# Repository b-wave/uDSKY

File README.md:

# uDSKY PROJECT
## A Physical implementaion of an Apollo AGC DSKY. 
*...with USB 2.0 Connectivity for PC simulators*

This assembly and firmware has sucessfully been used to control both
John Pultorak's Block1 Simulator vers 1.16 in C++ and Ronald Burkey's
Block 2 AGC simulators on <http://www.ibiblio.org/apollo/> 
Further, the Simulation runs great on Raspberry Pi.  I forked the 
files needed for both simulators. <https://github.com/b-wave/virtualagc> 

I mainly run it on a Rapsberry PI with the intention of embedding the Pi in this chassis. I started a 
python script that will run the software so I don't have to start the virtual AGC program.... 
now that is a *work in progress...stay tuned* 

The Teensy 3.2 used in this has a plug in board that contains a Real time clock and navigation sensors.
<https://www.pjrc.com/store/prop_shield.html>  Which will mount to the board nicely.  I also included a couple of Apollo-themed Processing PDEs in <https://github.com/b-wave/uDSKY/tree/master/uDSKY%20IMU>
that work with this board and it can mount to the uDSKY using stacking header pins. 

Why on earth did I do this project?  Ultimately, it is a clock. I intend to have a standalone
version to do navigation demonstation experiments and become a "moon clock" to track
the current position, phase, and distance to the moon - *...in real time!*

### What it is not... 
Its not to scale or even a 1:1 scale model of a DSKY.  How I arrived at the scaling was 
I took the best head-on photo of a DSKY I could find and scaled it to match the 
smallest descrete LED 7-segment *green-ish* displays I could find.
It turned out that at that scale, the Keys were  ~.75" on center, which was nice
eand almost exactly 0.75" Square. Also by happy accident the Teensey fits between the top LED
Displays. The front panel measurments was about 7.0" x 6.5" so about, but
not exactly, half the size of a real DSKY. You will see some early refernces to **mini-DSKY** 
Which is the same thing as **uDSKY**.  The whole thing sandwiches nicely together
using plexiglas plates - which I will provide laser cut patterns for - and #4 AWG hardware spacers.

The **uDSKY** assembly is remarkably sturdy and even kind of hefty too.  The keys and circuit 
boards were attached by small torx head "thread rolling" screws for plastic.  
The Torx heads allow for close proximity to components and I think a little easier to install straight.
The hardware I used were surplus and about 2 AWG, ( for a 1/16" pilot hole) and 1/8" long.  
I got them on e-bay and i don't have the link, there were 100's of them in a box for a few dollars. 
They should be easy to find. I'll update a link if I find a good supplier again. 

There are two other circuit boards I am developing.  The INDICATOR boards for the LEDs
since I used perf boards for this prototype.  The POWER REGULATOR board for stand alone
operation on 12V dc, and illuminating and controlling the VERB, NOUN, and PROG LEDs
and the keyboard backlighting. Since these are a lot of LEDs involved 12V is used for them. 
These will be controlled the same as the other LEDs using two of the non used DP signals
but thru an isolator to control 12V to theses diodes. I also have an idea to use LEDs
and some clear plexiglas to simulate the long EL strips between the three registers - 
 but this is still in the *idea phase*...but the testing is showing promise. 

uDSKY in action 9/20/19 on the 50th moonlanding, running on rPI and ran the *actual* Apollo 11 software (C055), mostly P00 for the entire duration of the flight.   This .gif was when they would have been in lunar orbit at 100hrs 38mins or so MET. 

Running Apollo 11 CMD Module Software. 

The circuit boards are mostly attached to a 1/8" plexiglas rear plate.  The Teensey is
mounted on female pin headers on the main display board.  The Teensy actully slips thru
a recetangular hole in the rear mounting plate. 

## Displays
The displays are multiplexed with the DP segments from the first two controlling the LED INDICATORS.  Each lamp is controlled by the decimal point signals, which were not used in the original Apollo DSKY display.  This turned out to be a good parts reduction
as all the segments and Indicators can be controlle by only 3 LED controller chips.

All Displays are ON!

Only the SEGMENT G and DP are used in the first display for each of the three registors
to provide the segments for the SIGN digit.  Since there is no known compatable SIGN LED Display - i put an array of SMT LEDs on the circuit board to represent this digit.

Every Other INDIC Lamp is On.

As you can see there is still some leakage between wells of the Indicator lamps but 
this is quite usable. 

The lamps are separated with a matrix of opaque lattius.  I made the prototype with popcicle
sticks, which turned out to be a litle short.  I made a 3D printed chassis wich is way better! 

Indicator Display Mask

In all the dispalys work fine, but later I realized that if the displays were behind a card stock printout, behind some smoked grey plexiglas they look a lot like the original Apollo DSKY EL displays.  But the LEDs were too far from the card stock to be seen.  I then developed a pair of circuit boards, one to hold the LEDs and the other provides a light mask. This brings the sign digit near to the display. 67lb. White Cover Card stock (Staples **Item 679482** to be exact).  I 

As you can see with the card stock the uDSKY is very simular to the DSKY as you cant really see the digits until they are
illuminated.  The only issue is the LED must be against the card stock for the effect to work.  I did not have the sign LED digit boards working, and the prototype had the LEDs soldered to the main board, which is too far away to be seen thru the card stock.  

*No digits seen With power off*

The 3D printed chasis is now on version 2.  Here are a couple of shots of the first parts.  It really started looking real, and as you can see from the .gif it is a lot better now than the original hand cut plexiglas. 

3D Parts

Keys and displays added

# Apollo uDSKY's  Keys 
The Keys are Cherry MX series. These have a real nice clicky feel and best of allthey can support custom keycaps and can be illuminated! 

#The key caps are from:  <http://xkeys.com/accessories/Keycaps.php> 
They are not .75" x .75 which would be ideal but they have a little curve on the bottom
which makes the laser printed labels a little tricky to line up. But it works fairly well.
You will need 19 caps (4 orders will get you 20). I got both the clear and green. I thnk the black ones
owill be opaque so they can't be illuminated. 

<Keys with relegendable keycaps for cherry mx switches

The Keys are simply mounted on an *OSH Park Version*  of the SF MX breakout board. You can order them 
#or (BOB-13773) they are identical: https://www.sparkfun.com/products/13773 The next version I make may contain all 19 keys in one board.  The 1 pins are all connected for ROWS and the 2 pins are for columns.
Check out the Teensey code for the pattern and hookup. 
<https://github.com/b-wave/uDSKY/tree/master/DSKY%20Arduino%20Files>

Breakout Column connections - using the 2 Pads.

The X/Y row - column pattern is fairly self-explanitory.  The final assembly feels like holding some chain-mail armor. 
The only difficulties were to use small wire "U" shapes instead of straight from pin to pin. This makes the 
spacing of the keys line up to the holes on the base plate a little eaiser.  The second is the two columns 
on the ends don't line up anyway on one side, it helps to flip those two end keys, the pads match and the keycap will
still go on correctly. *NOTE: see the flip keys on on the right hand side of bottom view:*

Matrix of Keys

# Apollo uDSKY's  Registers Sign Digits
I developed a little circuit board *set* that will give a sign digit for each register.  There are actully two other ways to 
get the sign digits. First, simply put in another 7-segment display. The G segment will be (-) and the DP will represent (+) 
...*blank is octal as usual*  Second, the board has pad for SMT LEDs that form the signs.  G and DP illumiate the pairs of
LEDs but this arrangement has the distance problem, but you can still use the mask board to make the displays look better.

This board will allow a pretty good substitute for the non-existent compatible LED sign digits for an **Apollo DSKY** display.  You will also need the   **DS_MASK.brd** <https://oshpark.com/shared_projects/6qTKqnak> for each display if you want the displays to be more *segment-ty?*   There are also some additional masking and diffusing techniques  that can be done to make these look really good.

##
This board set are intended to be used with a 0.39" 10-pin LED displays such as **LTS-4301G** that were used on the **uDSKY** display. 

The minus **(-)** are controlled by the standard *G - Segment* Pin **1** with 2 LEDs in series.  The **(+)** is a combination of the **"g1"**  and **"g2"** Segs *and* the vertical segments *(some times referred to as **"h"** and **"J"**)* which are connected to the **"DP"** pin **6**.  The **Common** pins are **8** and **3**.  Because both displays are *two* LEDs in series this should simplify non-MUX displays as well.

<https://www.jameco.com/z/LTS-4301G-Lite-On-Electronics-Green-7-Segment-LED-Display_2227911.html>

When selecting the SMT LEDs make sure you get them close to the brightness and color wavelength.  For example , these LED displays have: **569 nm**  (green) with an avg. intensity = **2200 µCD** @ If =10mA.

I can post some details on how to put these together.  But basically, you need to diffuse the light or the viewing angle gets critical.  A simple piece of scotch tape but hot melt glue may also work.  

The parts placement is pretty simple, The anode of the first LED connects to the respective pin.  The two LED's cathodes and anodes for each segment are connected together. The cathodes of the 2nd LEDs connect to the common pins.  If you forget one LED or get one in backwards it's like Christmas tree light strings... *no light for you!*  

Plus Display

A couple of baffles between the G and the vertical segments are also needed or when only (-) is displayed the other segments are still slightly visible.  I used a couple scrap pieces of black wire insulation wedged between the segments to block this.  The messy dabs of hot melt glue used to hold these in place are also visible.

Light Baffels 

Minus Display

Two 0.1" 5-pin headers to hold the two boards together.  Mount the header on *top* of this board (long pins go thru the board)   Then put the mask board on top of the header. The boards are separated by the plastic header. Push the pins flush to the  top **MSK_Brd** *Pins 1, 6, 8, and 3* now have to be soldered on the bottom of this board.  You can solder the mask board's pins all in place if you want to - after you verify everything is working OK of course, there are no electrical connections to any other pads.

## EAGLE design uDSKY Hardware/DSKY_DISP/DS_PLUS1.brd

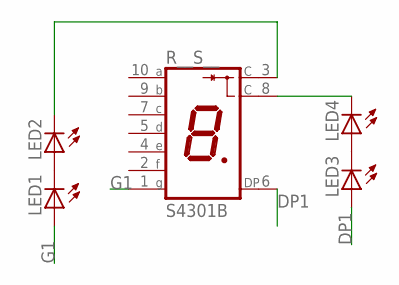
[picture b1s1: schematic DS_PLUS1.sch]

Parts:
LED1, LED2, LED3, LED4: LEDCHIP-LED0603; CHIP-LED0603
R__S__: S4301B

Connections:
DP1: LED3.A, R__S__.6 (DP)
G1: LED1.A, R__S__.1 (G)
unnamed: LED1.C, LED2.A
unnamed: LED3.C, LED4.A
unnamed: LED4.C, R__S__.8 (C)
unnamed: LED2.C, R__S__.3 (C)

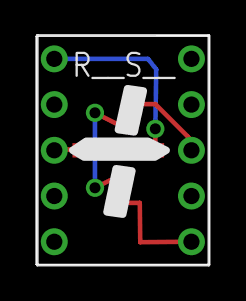
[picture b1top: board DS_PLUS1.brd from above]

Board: 2 copper layers, 9.7 x 12.7 mm, 5 parts (0 on the bottom side), 6 nets.

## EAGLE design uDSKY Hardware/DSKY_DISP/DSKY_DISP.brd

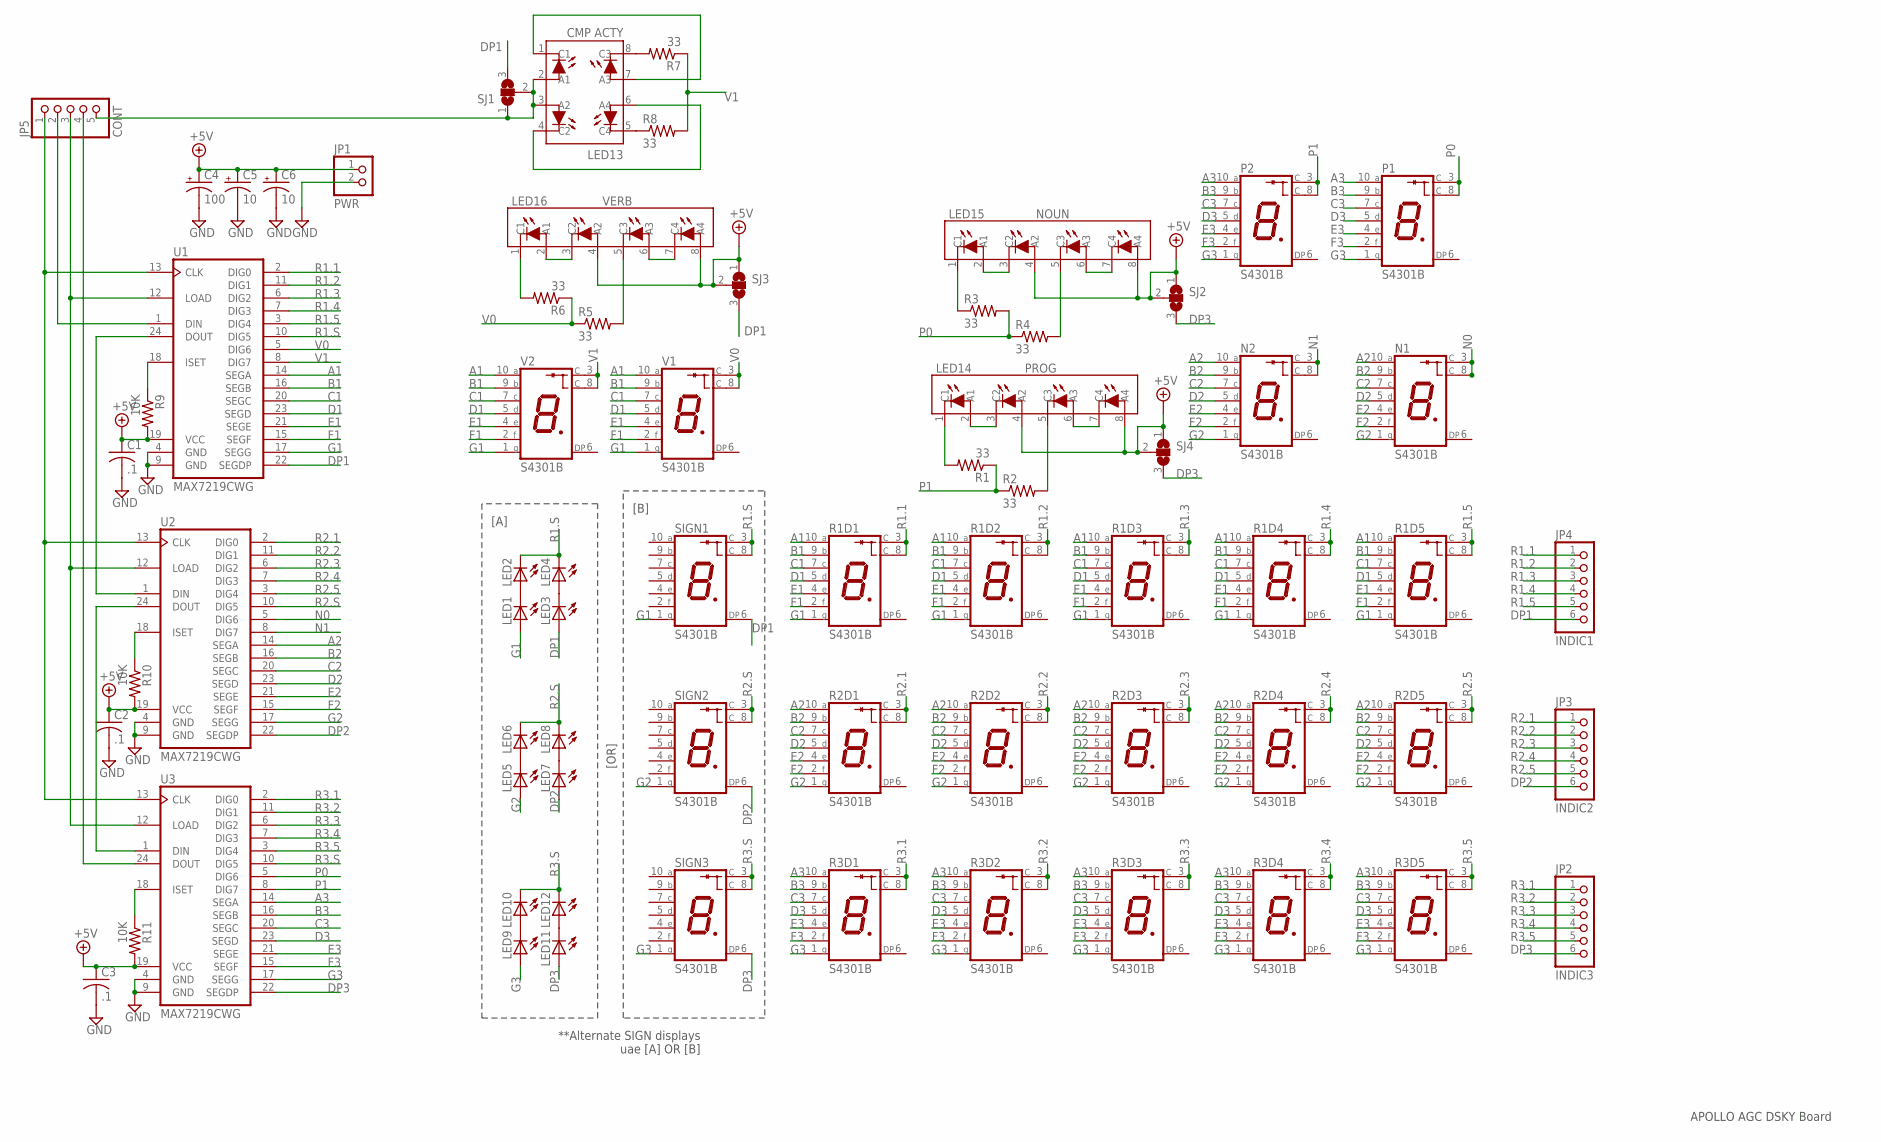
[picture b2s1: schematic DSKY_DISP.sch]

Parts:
C1, C2, C3: .1; C025-030X050
C4: 100; E2,5-6E
C5, C6: 10; E1,8-4
JP1: PWR; 1X02
JP2: INDIC3; 1X06
JP3: INDIC2; 1X06
JP4: INDIC1; 1X06
JP5: CONT; 1X05
LED1, LED2, LED3, LED4, LED5, LED6, LED7, LED8, LED9, LED10, LED11, LED12: LEDCHIPLED_0603; CHIPLED_0603
LED13: CMP ACTY; SOCKET-08
LED14: PROG; SIP-08
LED15: NOUN; SIP-08
LED16: VERB; SIP-08
N1, N2: S4301B
P1, P2: S4301B
R1, R2, R3, R4, R5, R6, R7, R8: 33; 0207/10
R1D1, R1D2, R1D3, R1D4, R1D5, R2D1, R2D2, R2D3, R2D4, R2D5, R3D1, R3D2, R3D3, R3D4, R3D5: S4301B
R9, R10, R11: 10K; 0207/10
SIGN1, SIGN2, SIGN3: S4301B
SJ1, SJ2, SJ3, SJ4: SJ2WW; SJ_2W
U1, U2, U3: MAX7219CWG; SO24W
V1, V2: S4301B

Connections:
+5V: C1.1, C2.1, C3.1, C4.+, C5.+, C6.+, JP1.1, LED14.4 (A2), LED14.8 (A4), LED15.4 (A2), LED15.8 (A4), LED16.4 (A2), LED16.8 (A4), R9.2, R10.2, R11.2, SJ2.1, SJ2.2, SJ3.1, SJ3.2, SJ4.1, SJ4.2, U1.19 (VCC), U2.19 (VCC), U3.19 (VCC)
A1: R1D1.10 (A), R1D2.10 (A), R1D3.10 (A), R1D4.10 (A), R1D5.10 (A), U1.14 (SEGA), V1.10 (A), V2.10 (A)
A2: N1.10 (A), N2.10 (A), R2D1.10 (A), R2D2.10 (A), R2D3.10 (A), R2D4.10 (A), R2D5.10 (A), U2.14 (SEGA)
A3: P1.10 (A), P2.10 (A), R3D1.10 (A), R3D2.10 (A), R3D3.10 (A), R3D4.10 (A), R3D5.10 (A), U3.14 (SEGA)
B1: R1D1.9 (B), R1D2.9 (B), R1D3.9 (B), R1D4.9 (B), R1D5.9 (B), U1.16 (SEGB), V1.9 (B), V2.9 (B)
B2: N1.9 (B), N2.9 (B), R2D1.9 (B), R2D2.9 (B), R2D3.9 (B), R2D4.9 (B), R2D5.9 (B), U2.16 (SEGB)
B3: P1.9 (B), P2.9 (B), R3D1.9 (B), R3D2.9 (B), R3D3.9 (B), R3D4.9 (B), R3D5.9 (B), U3.16 (SEGB)
C1: R1D1.7 (C), R1D2.7 (C), R1D3.7 (C), R1D4.7 (C), R1D5.7 (C), U1.20 (SEGC), V1.7 (C), V2.7 (C)
C2: N1.7 (C), N2.7 (C), R2D1.7 (C), R2D2.7 (C), R2D3.7 (C), R2D4.7 (C), R2D5.7 (C), U2.20 (SEGC)
C3: P1.7 (C), P2.7 (C), R3D1.7 (C), R3D2.7 (C), R3D3.7 (C), R3D4.7 (C), R3D5.7 (C), U3.20 (SEGC)
D1: R1D1.5 (D), R1D2.5 (D), R1D3.5 (D), R1D4.5 (D), R1D5.5 (D), U1.23 (SEGD), V1.5 (D), V2.5 (D)
D2: N1.5 (D), N2.5 (D), R2D1.5 (D), R2D2.5 (D), R2D3.5 (D), R2D4.5 (D), R2D5.5 (D), U2.23 (SEGD)
D3: P1.5 (D), P2.5 (D), R3D1.5 (D), R3D2.5 (D), R3D3.5 (D), R3D4.5 (D), R3D5.5 (D), U3.23 (SEGD)
DP1: JP4.6, LED3.A, SIGN1.6 (DP), SJ1.3, SJ3.3, U1.22 (SEGDP)
DP2: JP3.6, LED7.A, SIGN2.6 (DP), U2.22 (SEGDP)
DP3: JP2.6, LED11.A, SIGN3.6 (DP), SJ2.3, SJ4.3, U3.22 (SEGDP)
E1: R1D1.4 (E), R1D2.4 (E), R1D3.4 (E), R1D4.4 (E), R1D5.4 (E), U1.21 (SEGE), V1.4 (E), V2.4 (E)
E2: N1.4 (E), N2.4 (E), R2D1.4 (E), R2D2.4 (E), R2D3.4 (E), R2D4.4 (E), R2D5.4 (E), U2.21 (SEGE)
E3: P1.4 (E), P2.4 (E), R3D1.4 (E), R3D2.4 (E), R3D3.4 (E), R3D4.4 (E), R3D5.4 (E), U3.21 (SEGE)
F1: R1D1.2 (F), R1D2.2 (F), R1D3.2 (F), R1D4.2 (F), R1D5.2 (F), U1.15 (SEGF), V1.2 (F), V2.2 (F)
F2: N1.2 (F), N2.2 (F), R2D1.2 (F), R2D2.2 (F), R2D3.2 (F), R2D4.2 (F), R2D5.2 (F), U2.15 (SEGF)
F3: P1.2 (F), P2.2 (F), R3D1.2 (F), R3D2.2 (F), R3D3.2 (F), R3D4.2 (F), R3D5.2 (F), U3.15 (SEGF)
G1: LED1.A, R1D1.1 (G), R1D2.1 (G), R1D3.1 (G), R1D4.1 (G), R1D5.1 (G), SIGN1.1 (G), U1.17 (SEGG), V1.1 (G), V2.1 (G)
G2: LED5.A, N1.1 (G), N2.1 (G), R2D1.1 (G), R2D2.1 (G), R2D3.1 (G), R2D4.1 (G), R2D5.1 (G), SIGN2.1 (G), U2.17 (SEGG)
G3: LED9.A, P1.1 (G), P2.1 (G), R3D1.1 (G), R3D2.1 (G), R3D3.1 (G), R3D4.1 (G), R3D5.1 (G), SIGN3.1 (G), U3.17 (SEGG)
GND: C1.2, C2.2, C3.2, C4.-, C5.-, C6.-, JP1.2, U1.4 (GND), U1.9 (GND), U2.4 (GND), U2.9 (GND), U3.4 (GND), U3.9 (GND)
N0: N1.3 (C), N1.8 (C), U2.5 (DIG6)
N1: N2.3 (C), N2.8 (C), U2.8 (DIG7)
unnamed: LED1.C, LED2.A
unnamed: LED3.C, LED4.A
unnamed: LED5.C, LED6.A
unnamed: LED7.C, LED8.A
unnamed: LED11.C, LED12.A
unnamed: LED9.C, LED10.A
unnamed: LED14.6 (A3), LED14.7 (C4)
unnamed: LED14.2 (A1), LED14.3 (C2)
unnamed: LED15.6 (A3), LED15.7 (C4)
unnamed: LED15.2 (A1), LED15.3 (C2)
unnamed: LED16.6 (A3), LED16.7 (C4)
unnamed: LED16.2 (A1), LED16.3 (C2)
unnamed: LED13.1 (C1), LED13.7 (A3)
unnamed: LED13.4 (C2), LED13.6 (A4)
unnamed: LED14.1 (C1), R1.2
unnamed: LED14.5 (C3), R2.2
unnamed: LED13.8 (C3), R7.2
unnamed: LED15.1 (C1), R3.1
unnamed: LED15.5 (C3), R4.2
unnamed: LED13.5 (C4), R8.1
unnamed: LED16.5 (C3), R5.2
unnamed: LED16.1 (C1), R6.2
unnamed: JP5.2, U1.1 (DIN)
unnamed: U1.24 (DOUT), U2.1 (DIN)
unnamed: U2.24 (DOUT), U3.1 (DIN)
unnamed: JP5.3, U1.12 (LOAD), U2.12 (LOAD), U3.12 (LOAD)
unnamed: JP5.1, U1.13 (CLK), U2.13 (CLK), U3.13 (CLK)
unnamed: JP5.4, U3.24 (DOUT)
unnamed: R9.1, U1.18 (ISET)
unnamed: R10.1, U2.18 (ISET)
unnamed: R11.1, U3.18 (ISET)
unnamed: JP5.5, LED13.2 (A1), LED13.3 (A2), SJ1.1, SJ1.2
P0: P1.3 (C), P1.8 (C), R3.2, R4.1, U3.5 (DIG6)
P1: P2.3 (C), P2.8 (C), R1.1, R2.1, U3.8 (DIG7)
R1.1: JP4.1, R1D1.3 (C), R1D1.8 (C), U1.2 (DIG0)
R1.2: JP4.2, R1D2.3 (C), R1D2.8 (C), U1.11 (DIG1)
R1.3: JP4.3, R1D3.3 (C), R1D3.8 (C), U1.6 (DIG2)
R1.4: JP4.4, R1D4.3 (C), R1D4.8 (C), U1.7 (DIG3)
R1.5: JP4.5, R1D5.3 (C), R1D5.8 (C), U1.3 (DIG4)
R1.S: LED2.C, LED4.C, SIGN1.3 (C), SIGN1.8 (C), U1.10 (DIG5)
R2.1: JP3.1, R2D1.3 (C), R2D1.8 (C), U2.2 (DIG0)
R2.2: JP3.2, R2D2.3 (C), R2D2.8 (C), U2.11 (DIG1)
R2.3: JP3.3, R2D3.3 (C), R2D3.8 (C), U2.6 (DIG2)
R2.4: JP3.4, R2D4.3 (C), R2D4.8 (C), U2.7 (DIG3)
R2.5: JP3.5, R2D5.3 (C), R2D5.8 (C), U2.3 (DIG4)
R2.S: LED6.C, LED8.C, SIGN2.3 (C), SIGN2.8 (C), U2.10 (DIG5)
R3.1: JP2.1, R3D1.3 (C), R3D1.8 (C), U3.2 (DIG0)
R3.2: JP2.2, R3D2.3 (C), R3D2.8 (C), U3.11 (DIG1)
R3.3: JP2.3, R3D3.3 (C), R3D3.8 (C), U3.6 (DIG2)
R3.4: JP2.4, R3D4.3 (C), R3D4.8 (C), U3.7 (DIG3)
R3.5: JP2.5, R3D5.3 (C), R3D5.8 (C), U3.3 (DIG4)
R3.S: LED10.C, LED12.C, SIGN3.3 (C), SIGN3.8 (C), U3.10 (DIG5)
V0: R5.1, R6.1, U1.5 (DIG6), V1.3 (C), V1.8 (C)
V1: R7.1, R8.2, U1.8 (DIG7), V2.3 (C), V2.8 (C)

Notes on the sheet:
[OR]
**Alternate SIGN displays uae [A] OR [B]
[A]
[B]
APOLLO AGC DSKY Board

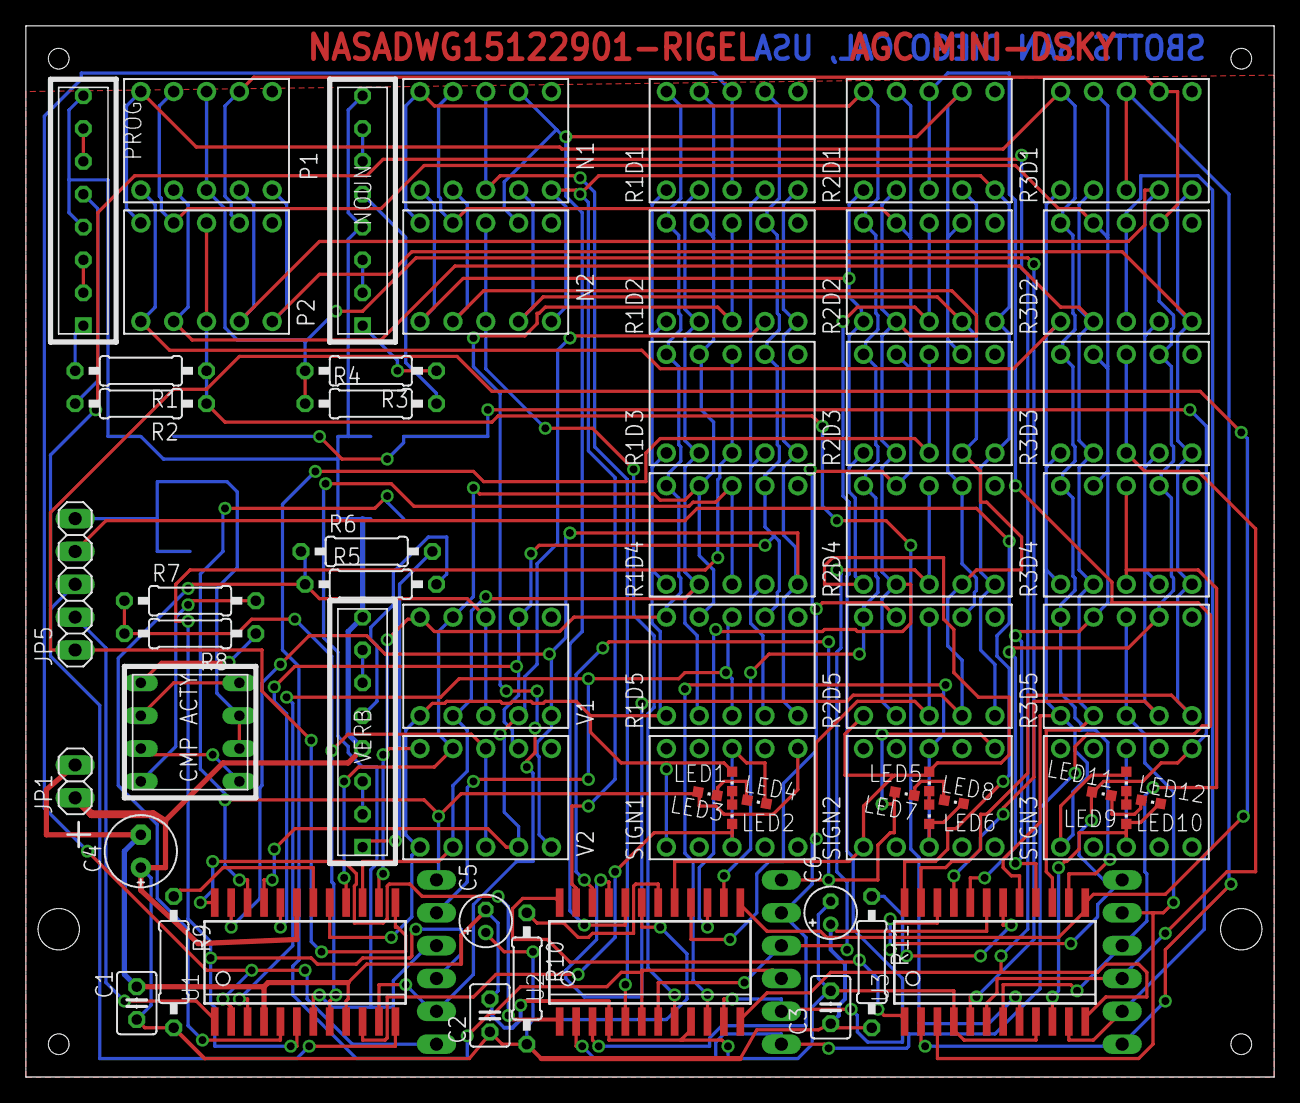
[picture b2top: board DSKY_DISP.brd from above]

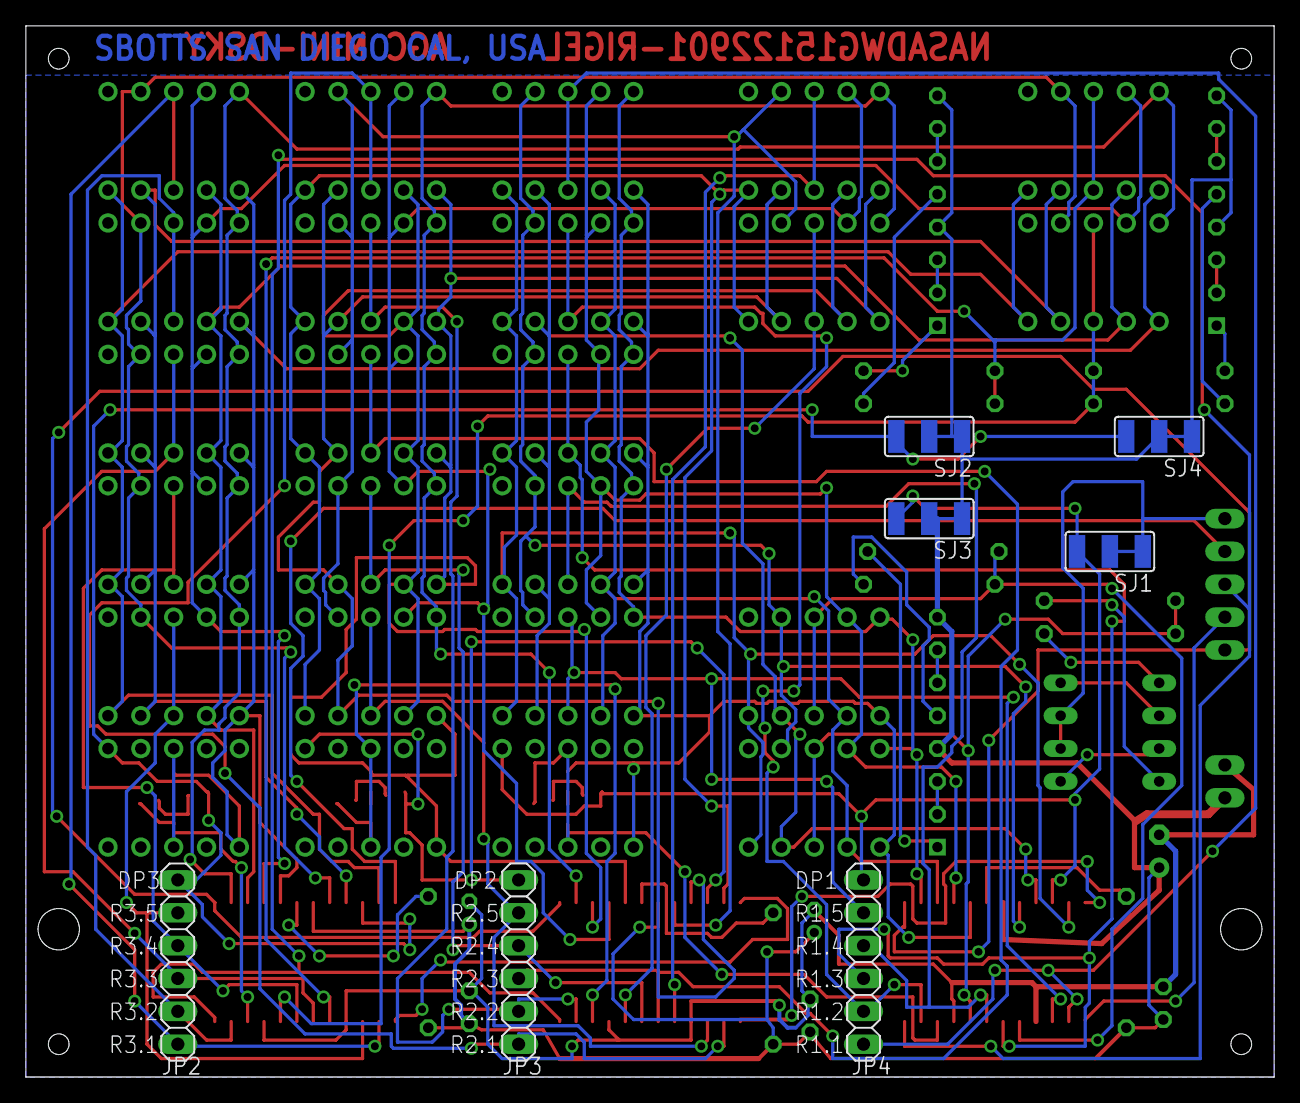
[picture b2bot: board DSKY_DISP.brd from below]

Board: 2 copper layers, 96.5 x 81.3 mm, 69 parts (7 on the bottom side), 82 nets.

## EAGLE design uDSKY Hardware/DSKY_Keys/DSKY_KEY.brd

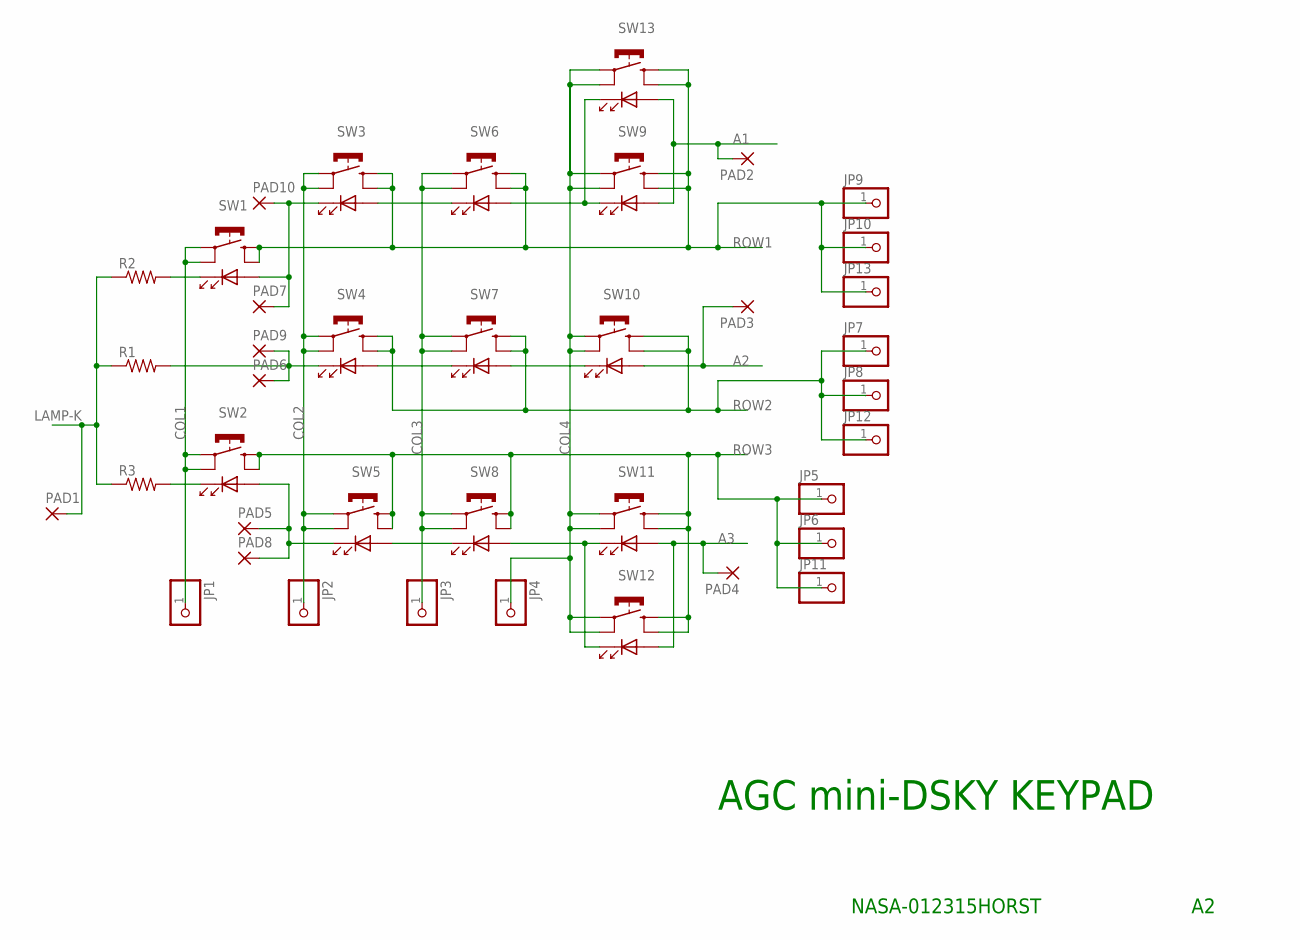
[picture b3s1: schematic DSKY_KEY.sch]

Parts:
JP1, JP2, JP3, JP4, JP5, JP6, JP7, JP8, JP9, JP10, JP11, JP12, JP13: PINHD-1X1; 1X01
PAD1: 2,54/0,8
PAD2, PAD3, PAD4, PAD5, PAD6, PAD7, PAD8, PAD9, PAD10: 1,6/0,8
R1, R2, R3: R-US_0204/7; 0204/7
SW1, SW2, SW3, SW4, SW5, SW6, SW7, SW8, SW9, SW10, SW11, SW12, SW13: B3E-1100; B3E-11XX

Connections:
A1: PAD2.1, SW9.P$5 (A), SW13.P$5 (A)
A2: PAD3.1, SW10.P$5 (A)
A3: PAD4.1, SW11.P$5 (A), SW12.P$5 (A)
COL1: JP1.1, SW1.P$1, SW1.P$2 (P1), SW2.P$1, SW2.P$2 (P1)
COL2: JP2.1, SW3.P$1, SW3.P$2 (P1), SW4.P$1, SW4.P$2 (P1), SW5.P$1, SW5.P$2 (P1)
COL3: JP3.1, SW6.P$1, SW6.P$2 (P1), SW7.P$1, SW7.P$2 (P1), SW8.P$1, SW8.P$2 (P1)
COL4: JP4.1, SW9.P$1, SW9.P$2 (P1), SW10.P$1, SW10.P$2 (P1), SW11.P$1, SW11.P$2 (P1), SW12.P$1, SW12.P$2 (P1), SW13.P$1, SW13.P$2 (P1)
LAMP-K: PAD1.1, R1.1, R2.1, R3.1
unnamed: R2.2, SW1.P$6 (K)
unnamed: R3.2, SW2.P$6 (K)
unnamed: PAD6.1, PAD9.1, R1.2, SW4.P$6 (K)
unnamed: SW8.P$5 (A), SW11.P$6 (K), SW12.P$6 (K)
unnamed: SW6.P$5 (A), SW9.P$6 (K), SW13.P$6 (K)
unnamed: SW5.P$5 (A), SW8.P$6 (K)
unnamed: PAD5.1, PAD8.1, SW2.P$5 (A), SW5.P$6 (K)
unnamed: SW7.P$5 (A), SW10.P$6 (K)
unnamed: SW4.P$5 (A), SW7.P$6 (K)
unnamed: PAD7.1, PAD10.1, SW1.P$5 (A), SW3.P$6 (K)
unnamed: SW3.P$5 (A), SW6.P$6 (K)
ROW1: JP9.1, JP10.1, JP13.1, SW1.P$3 (S), SW1.P$4 (S1), SW3.P$3 (S), SW3.P$4 (S1), SW6.P$3 (S), SW6.P$4 (S1), SW9.P$3 (S), SW9.P$4 (S1), SW13.P$3 (S), SW13.P$4 (S1)
ROW2: JP7.1, JP8.1, JP12.1, SW4.P$3 (S), SW4.P$4 (S1), SW7.P$3 (S), SW7.P$4 (S1), SW10.P$3 (S), SW10.P$4 (S1)
ROW3: JP5.1, JP6.1, JP11.1, SW2.P$3 (S), SW2.P$4 (S1), SW5.P$3 (S), SW5.P$4 (S1), SW8.P$3 (S), SW8.P$4 (S1), SW11.P$3 (S), SW11.P$4 (S1), SW12.P$3 (S), SW12.P$4 (S1)

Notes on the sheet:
AGC mini-DSKY KEYPAD
NASA-012315HORST

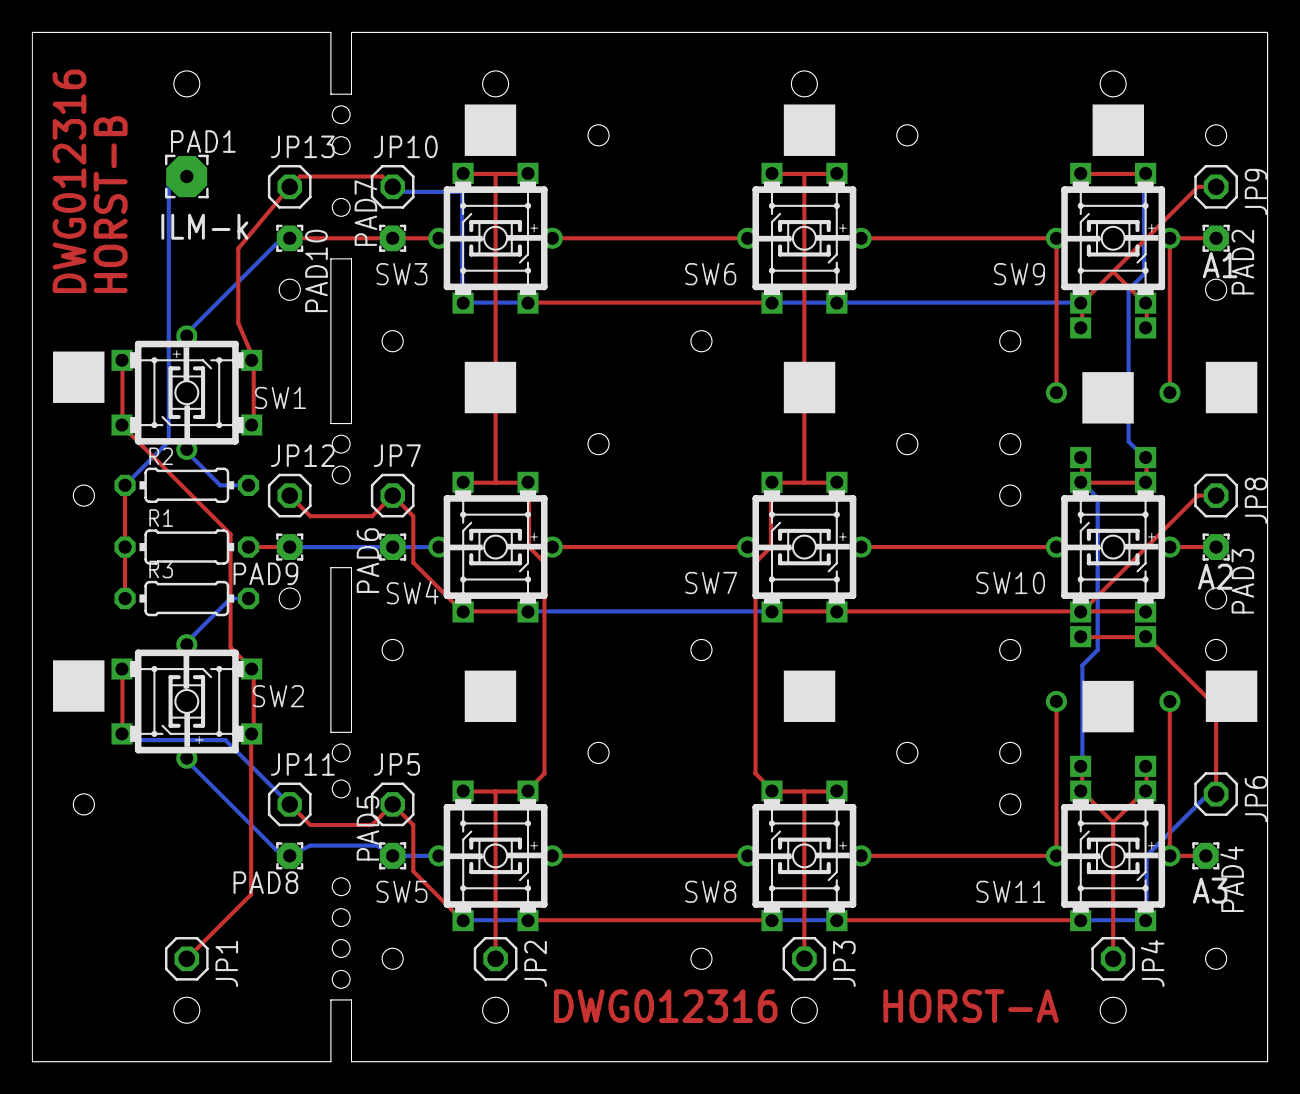
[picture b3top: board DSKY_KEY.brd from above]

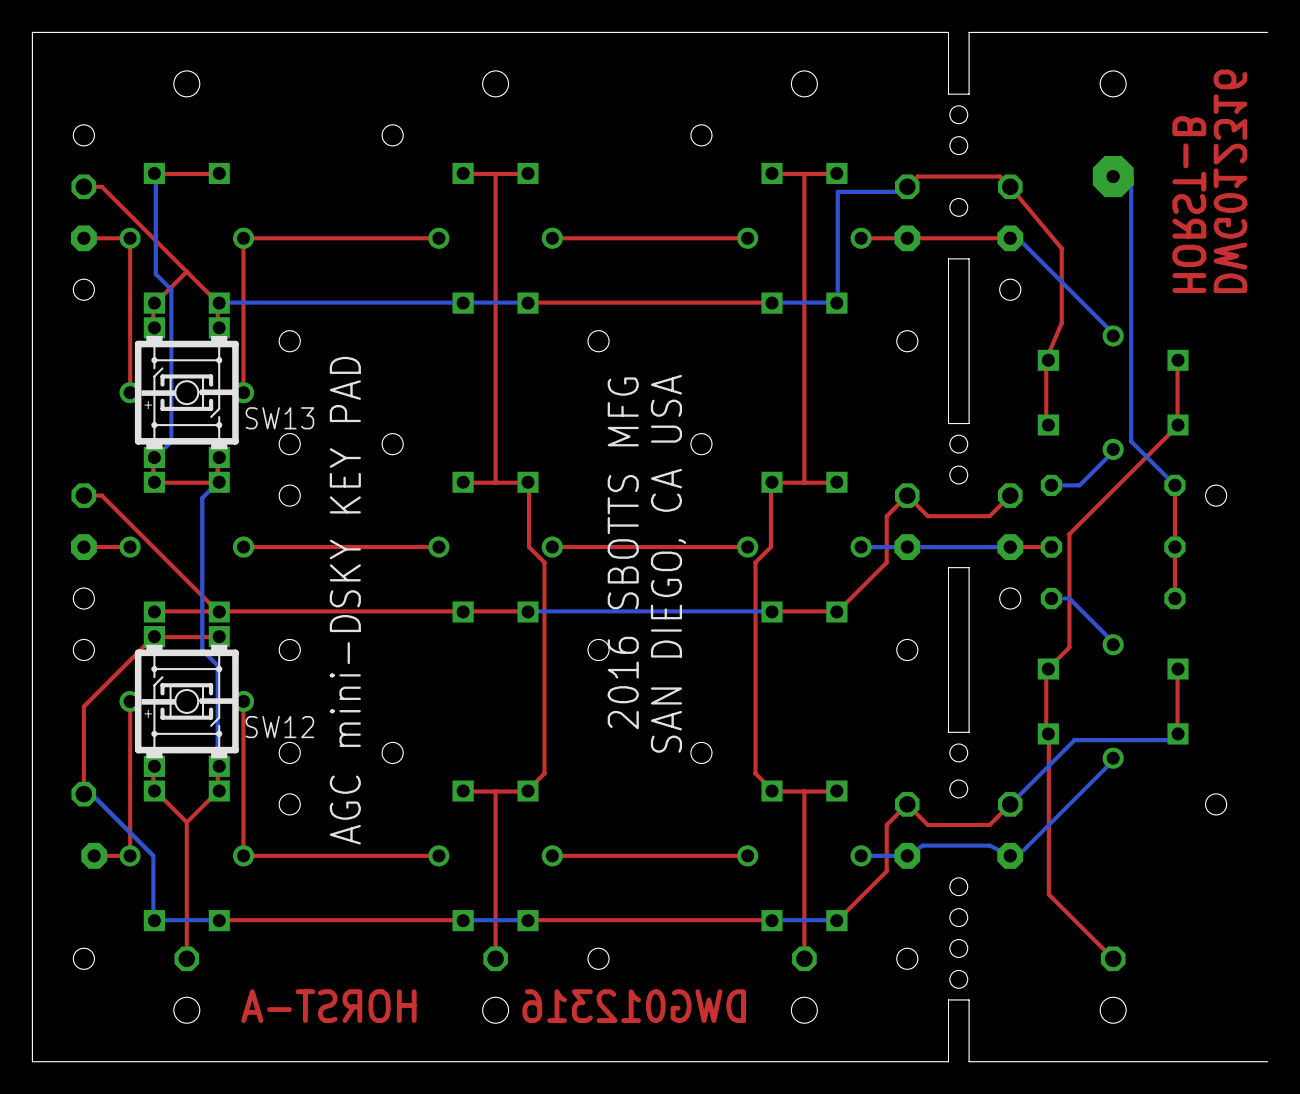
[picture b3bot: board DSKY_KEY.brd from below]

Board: 2 copper layers, 76.2 x 63.5 mm, 39 parts (2 on the bottom side), 22 nets.

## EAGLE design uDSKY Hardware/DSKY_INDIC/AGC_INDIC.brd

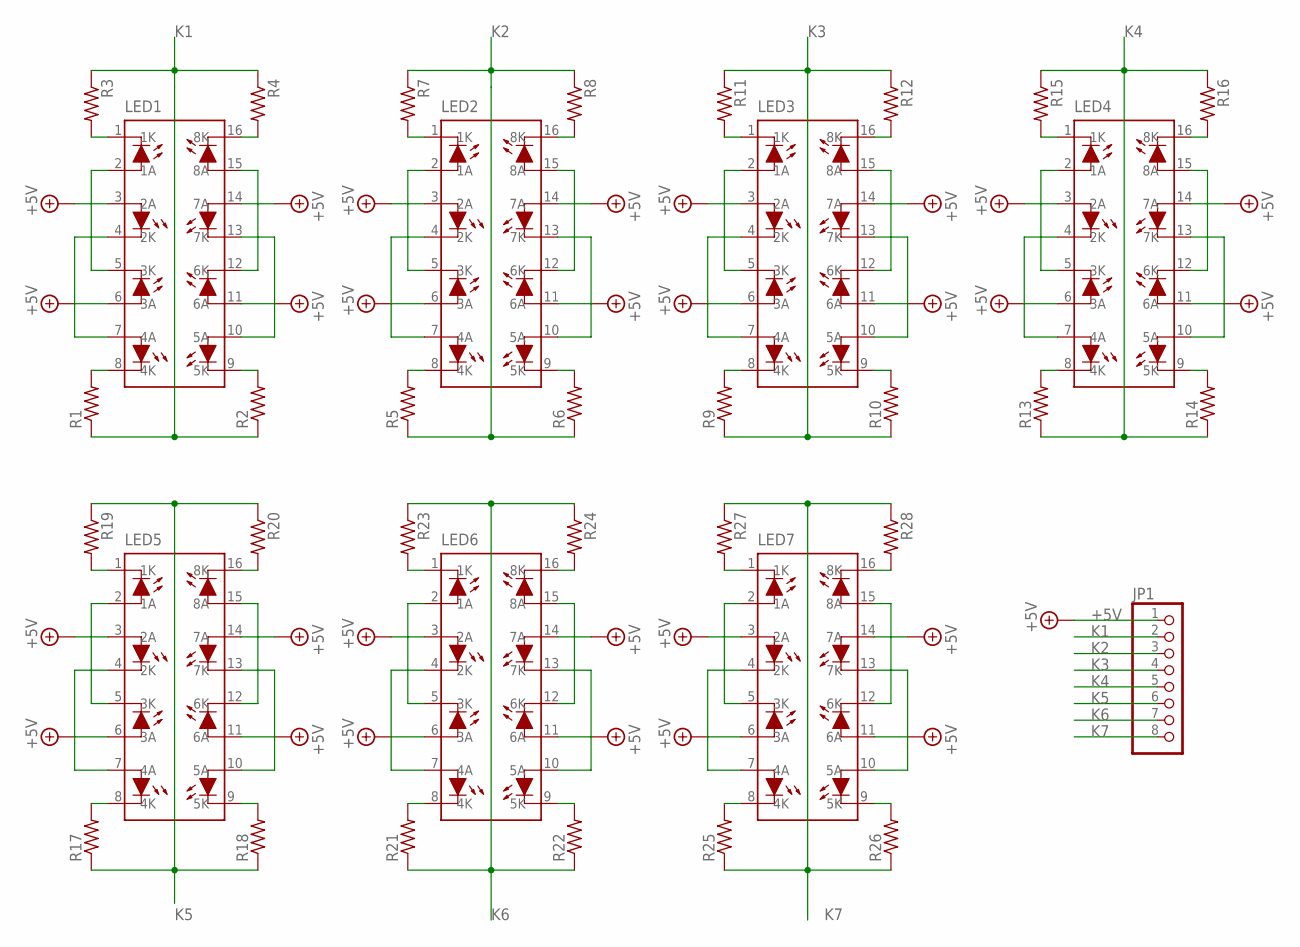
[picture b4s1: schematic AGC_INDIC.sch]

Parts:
JP1: PINHD-1X8; 1X08
LED1, LED2, LED3, LED4, LED5, LED6, LED7: HCLP-E; E100-16
R1, R2, R3, R4, R5, R6, R7, R8, R9, R10, R11, R12, R13, R14, R15, R16, R17, R18, R19, R20, R21, R22, R23, R24, R25, R26, R27, R28: R-US_0204/5; 0204/5

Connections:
+5V: JP1.1, LED1.3 (2A), LED1.6 (3A), LED1.11 (6A), LED1.14 (7A), LED2.3 (2A), LED2.6 (3A), LED2.11 (6A), LED2.14 (7A), LED3.3 (2A), LED3.6 (3A), LED3.11 (6A), LED3.14 (7A), LED4.3 (2A), LED4.6 (3A), LED4.11 (6A), LED4.14 (7A), LED5.3 (2A), LED5.6 (3A), LED5.11 (6A), LED5.14 (7A), LED6.3 (2A), LED6.6 (3A), LED6.11 (6A), LED6.14 (7A), LED7.3 (2A), LED7.6 (3A), LED7.11 (6A), LED7.14 (7A)
K1: JP1.2, R1.1, R2.1, R3.1, R4.1
K2: JP1.3, R5.1, R6.1, R7.1, R8.1
K3: JP1.4, R9.1, R10.1, R11.1, R12.1
K4: JP1.5, R13.1, R14.1, R15.1, R16.1
K5: JP1.6, R17.1, R18.1, R19.1, R20.1
K6: JP1.7, R21.1, R22.1, R23.1, R24.1
K7: JP1.8, R25.1, R26.1, R27.1, R28.1
unnamed: LED1.2 (1A), LED1.5 (3K)
unnamed: LED1.4 (2K), LED1.7 (4A)
unnamed: LED1.12 (6K), LED1.15 (8A)
unnamed: LED1.10 (5A), LED1.13 (7K)
unnamed: LED1.8 (4K), R1.2
unnamed: LED1.9 (5K), R2.2
unnamed: LED1.1 (1K), R3.2
unnamed: LED1.16 (8K), R4.2
unnamed: LED2.2 (1A), LED2.5 (3K)
unnamed: LED2.4 (2K), LED2.7 (4A)
unnamed: LED2.12 (6K), LED2.15 (8A)
unnamed: LED2.10 (5A), LED2.13 (7K)
unnamed: LED2.8 (4K), R5.2
unnamed: LED2.9 (5K), R6.2
unnamed: LED2.1 (1K), R7.2
unnamed: LED2.16 (8K), R8.2
unnamed: LED3.2 (1A), LED3.5 (3K)
unnamed: LED3.4 (2K), LED3.7 (4A)
unnamed: LED3.12 (6K), LED3.15 (8A)
unnamed: LED3.10 (5A), LED3.13 (7K)
unnamed: LED3.8 (4K), R9.2
unnamed: LED3.9 (5K), R10.2
unnamed: LED3.1 (1K), R11.2
unnamed: LED3.16 (8K), R12.2
unnamed: LED4.2 (1A), LED4.5 (3K)
unnamed: LED4.4 (2K), LED4.7 (4A)
unnamed: LED4.12 (6K), LED4.15 (8A)
unnamed: LED4.10 (5A), LED4.13 (7K)
unnamed: LED4.8 (4K), R13.2
unnamed: LED4.9 (5K), R14.2
unnamed: LED4.1 (1K), R15.2
unnamed: LED4.16 (8K), R16.2
unnamed: LED5.2 (1A), LED5.5 (3K)
unnamed: LED5.4 (2K), LED5.7 (4A)
unnamed: LED5.12 (6K), LED5.15 (8A)
unnamed: LED5.10 (5A), LED5.13 (7K)
unnamed: LED5.8 (4K), R17.2
unnamed: LED5.9 (5K), R18.2
unnamed: LED5.1 (1K), R19.2
unnamed: LED5.16 (8K), R20.2
unnamed: LED6.2 (1A), LED6.5 (3K)
unnamed: LED6.4 (2K), LED6.7 (4A)
unnamed: LED6.12 (6K), LED6.15 (8A)
unnamed: LED6.10 (5A), LED6.13 (7K)
unnamed: LED6.8 (4K), R21.2
unnamed: LED6.9 (5K), R22.2
unnamed: LED6.1 (1K), R23.2
unnamed: LED6.16 (8K), R24.2
unnamed: LED7.2 (1A), LED7.5 (3K)
unnamed: LED7.4 (2K), LED7.7 (4A)
unnamed: LED7.12 (6K), LED7.15 (8A)
unnamed: LED7.10 (5A), LED7.13 (7K)
unnamed: LED7.8 (4K), R25.2
unnamed: LED7.9 (5K), R26.2
unnamed: LED7.1 (1K), R27.2
unnamed: LED7.16 (8K), R28.2

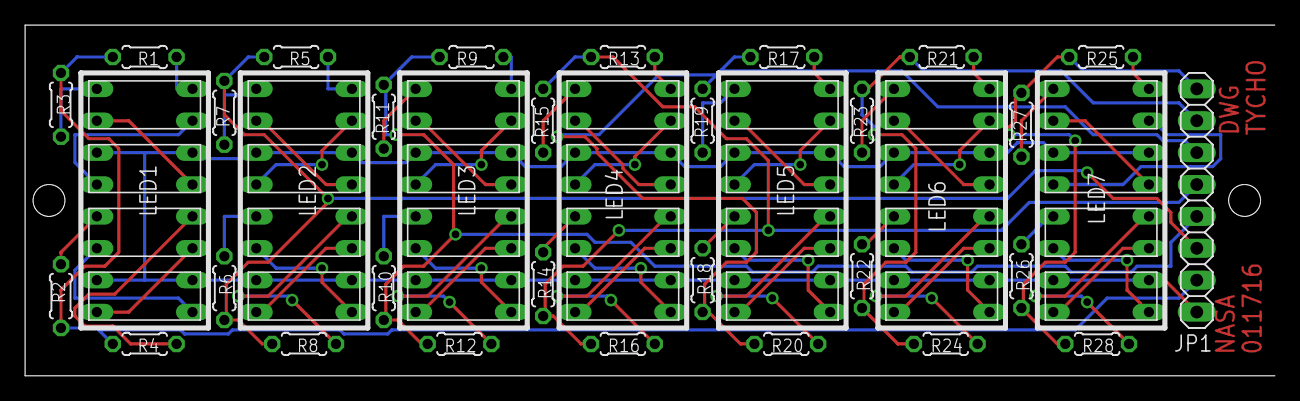
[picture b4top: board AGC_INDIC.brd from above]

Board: 2 copper layers, 99.6 x 27.9 mm, 36 parts (0 on the bottom side), 64 nets.

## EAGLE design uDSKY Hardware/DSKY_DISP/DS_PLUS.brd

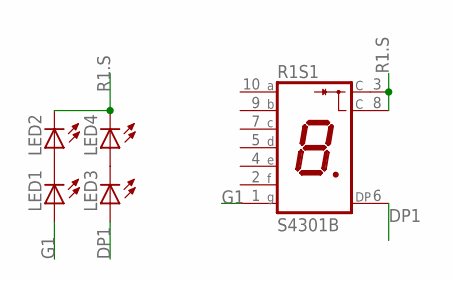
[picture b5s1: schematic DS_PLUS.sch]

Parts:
LED1, LED2, LED3, LED4: LEDCHIP-LED0603; CHIP-LED0603
R1S1: S4301B

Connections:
DP1: LED3.A, R1S1.6 (DP)
G1: LED1.A, R1S1.1 (G)
unnamed: LED1.C, LED2.A
unnamed: LED3.C, LED4.A
R1.S: LED2.C, LED4.C, R1S1.3 (C), R1S1.8 (C)

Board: 2 copper layers, 5 parts (0 on the bottom side), 5 nets, no tracks yet.

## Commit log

2017-09-01 Add files via upload
    Eagle Files
2017-09-01 Teensey controller files
2017-09-02 Add files via upload
    Processing files to demonstrate 9DOF IMU - not yet part of uDSKY
2017-09-03 Update readme.txt
    Added URL for PJRC prop Shield
2017-09-09 Update README.md
    edited description of displays and keys.
2017-09-26 Add files via upload
    Pics of Sign Digit Displays added
2017-09-26 Update README.md
    added sign digits discription
2017-09-26 Update README.md
    Added picture of Sign Digits
2017-09-26 Add files via upload
    Rotate Sign Digit pics
2017-09-26 Update README.md
    Keys
2017-09-26 Update README.md
    Added Keys, Displays Descriptions and added more Introduction
2017-09-26 Update README.md
    Spelling and typos
2017-12-08 changed from RTF and added example uses
2020-08-09 More recent photos
2020-08-09 uDSKY Running .gif
    Apollo 11 CMD Module SW
2020-08-09 3D printed chassis
2020-08-09 Better INDIC Holder Pic
2020-08-09 3D parts Pictures added
2020-08-10 edits
2020-08-10 Point to my virtualagc fork
    Demo shown running and some other edits
2020-08-15 Crop to show display only
2020-08-15 Update LED Display
    Better description of how to simulate the EL display with LEDs
2022-11-08 Update README.md
    edit read me

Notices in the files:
uDSKY Hardware/DSKY_DISP/DS_PLUS1.brd:
(c)2016 SB
uDSKY Hardware/DSKY_INDIC/AGC_INDIC.brd:
(c) 2016
